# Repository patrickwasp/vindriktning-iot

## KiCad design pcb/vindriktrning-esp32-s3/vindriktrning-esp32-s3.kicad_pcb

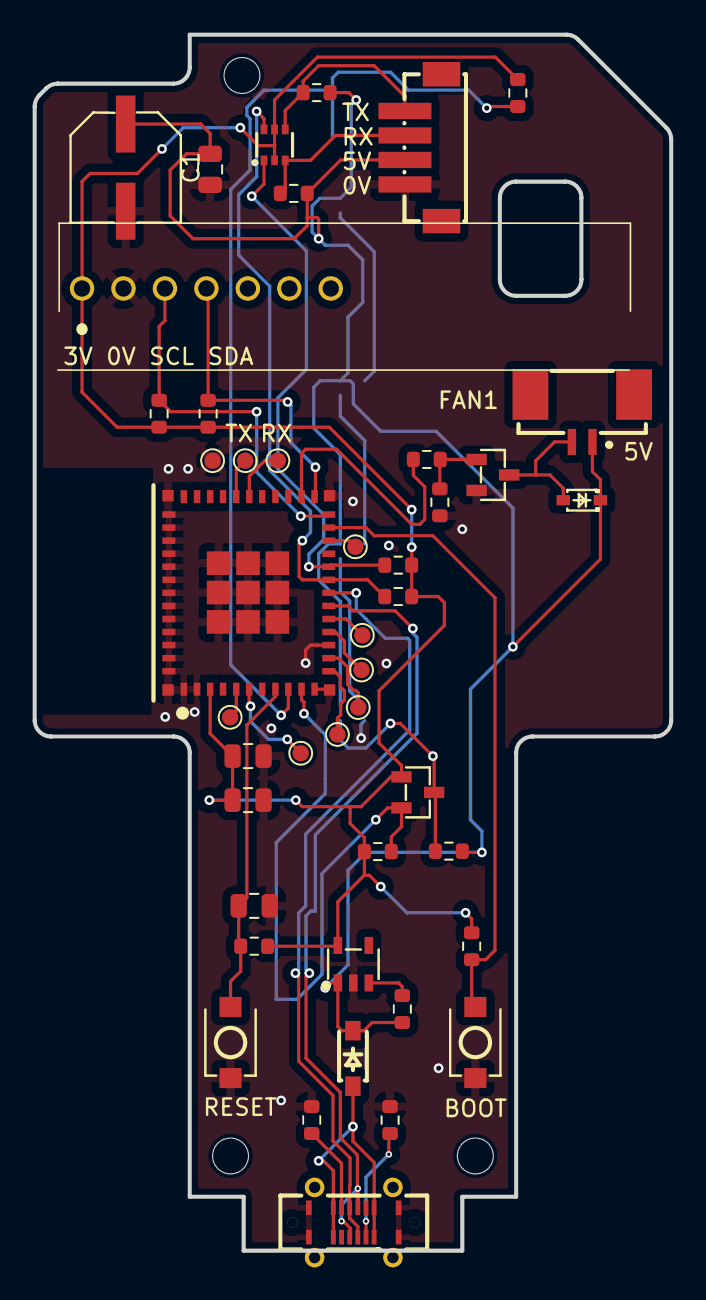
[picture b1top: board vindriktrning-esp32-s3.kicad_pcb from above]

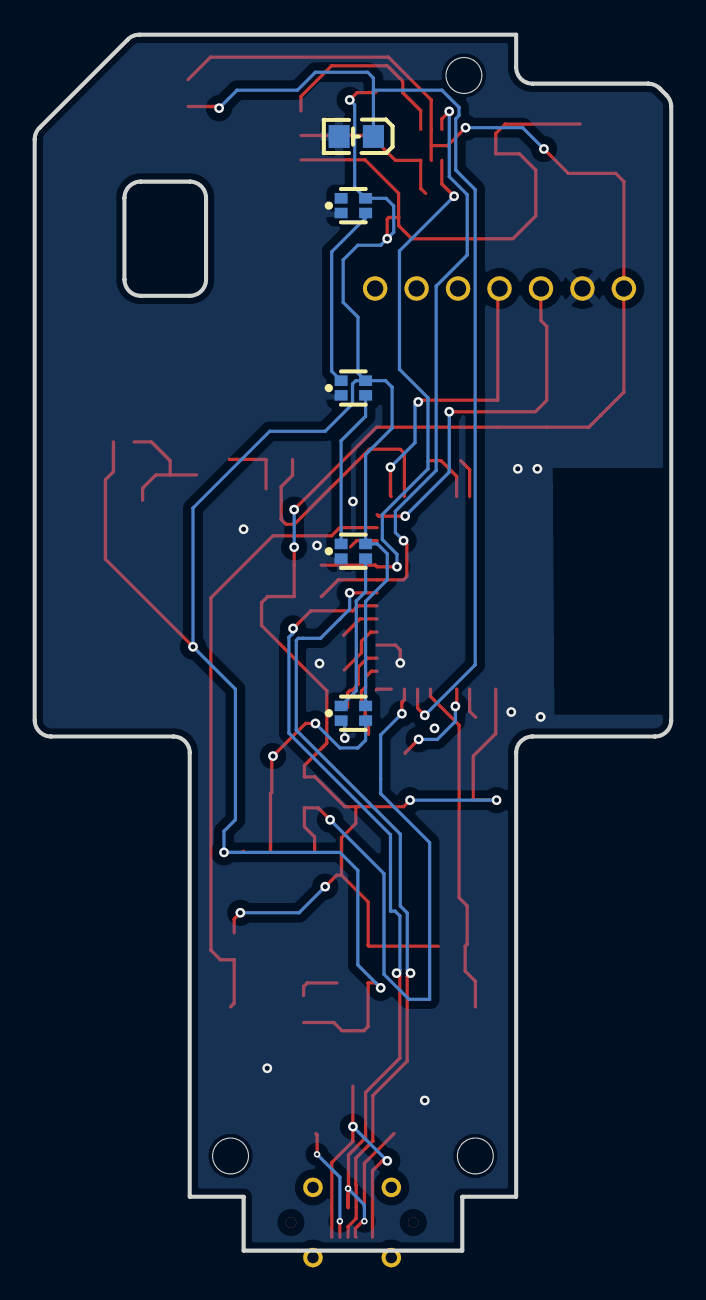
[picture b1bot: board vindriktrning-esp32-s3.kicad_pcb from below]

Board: 4 copper layers, 39.0 x 74.5 mm, 52 parts (5 on the bottom side), 35 nets.

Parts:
C1: 470uF; CAP-SMD_BD6.3-L6.6-W6.6-FD
C2, C3: 10uF; C_0805_2012Metric
C4: 10nF; C_0805_2012Metric
C5: 1uF; C_0805_2012Metric
FAN1: 1.25-2P; CONN-SMD_1.25-2P
H1, H2, H3: MountingHole; MountingHole_2.2mm_M2
IC1: SCD30
J1: P2.5; CONN-SMD_ZH1.5-4AB
J2, J3, J4, J5, J6, J7, J8, J9, J10, J11: Conn_01x01_Pin; TestPoint_Pad_D1.0mm
LED1: D10; LED-SMD_4P-L1.6-W1.5_XL-1615RGBC-WS2812B
LED2: D11; LED-SMD_4P-L1.6-W1.5_XL-1615RGBC-WS2812B
LED3: D12; LED-SMD_4P-L1.6-W1.5_XL-1615RGBC-WS2812B
LED4: D13; LED-SMD_4P-L1.6-W1.5_XL-1615RGBC-WS2812B
Q1: AO3400A_C347475; SOT-23-3_L2.9-W1.3-P1.90-LS2.4-BR
Q2: BSD840NH6327XTSA1; SC-70-6_L2.2-W1.3-P0.65-LS2.1-BR
Q3: BSS138; SOT-23-3_L2.9-W1.3-P1.90-LS2.4-BR
R1, R5, R11, R12, R13: 5.1k; R_0603_1608Metric
R2, R7, R8, R9, R10, R14: 10k; R_0603_1608Metric
R3, R4, R6, R16: 100k; R_0603_1608Metric
R15: 1k; R_0603_1608Metric
SW1: RESET Swtich; SW-SMD_L3.9-W3.0-P4.45
SW2: BOOT Switch; SW-SMD_L3.9-W3.0-P4.45
U1: SMD0805-20; OPTO-SMD_SMD0805-20
U2: D1; SOD-123_L2.7-W1.6-LS3.7-RD-1
U3: 1N5819; SOD-323_L1.7-W1.3-LS2.6-RD-1
U4: RT9080-33GJ5; TSOT-23-5_L2.9-W1.6-P0.95-LS2.8-BL
U6: ESP32-C6-MINI-1-N4; WIFIM-SMD_61P-L16.6-W13.2-P0.80-ESP32-C6-MINI-1-N4
USB1: GT-USB-7055BB; USB-C-TH_GT-USB-7055BB

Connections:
5VIN: U2.2 (A), USB1.A4 (VBUS), USB1.A9 (VBUS), USB1.B4 (VBUS), USB1.B9 (VBUS)
+3V3: C3.1, C4.1, IC1.1 (VDD), Q2.2 (G1), Q2.5 (G2), Q3.1 (G), R2.1, R7.1, R10.1, R11.1, R12.2, R13.2, R14.1, R16.1, U4.5 (VOUT), U6.3 (3V3)
+5V: C1.1, C2.1, FAN1.1, J1.3, LED1.2 (VDD), LED2.2 (VDD), LED3.2 (VDD), LED4.2 (VDD), R6.1, R8.2, R9.2, R15.1, U2.1 (K), U3.1 (C), U4.1 (VIN)
BOOT: R16.2, SW2.2, U6.23 (IO9)
CC1: R1.1, USB1.A5 (CC1)
CC2: R5.1, USB1.B5 (CC2)
D+: U6.18 (IO13), USB1.A6 (D+), USB1.B6 (D+)
D-: U6.17 (IO12), USB1.A7 (D-), USB1.B7 (D-)
FAN: R3.1, U6.26 (IO20)
GND: C1.2, C2.2, C3.2, C4.2, C5.2, IC1.2 (GND), J1.4, J4.1, LED1.3 (GND), LED2.3 (GND), LED3.3 (GND), LED4.3 (GND), Q1.2 (S), R1.2, R4.2, R5.2, SW1.1, SW2.1, U1.1 (E), U4.2 (GND), U6.1 (GND), U6.2 (GND), U6.11 (GND), U6.14 (GND), U6.36 (GND), U6.37 (GND), U6.38 (GND), U6.39 (GND), U6.40 (GND), U6.41 (GND), U6.42 (GND), U6.43 (GND), U6.44 (GND), U6.45 (GND), U6.46 (GND), U6.47 (GND), U6.48 (GND), U6.49 (GND), U6.50 (GND), U6.51 (GND), U6.52 (GND), U6.53 (GND), USB1.A1 (GND), USB1.A12 (GND), USB1.B1 (GND), USB1.B12 (GND)
IO0: J7.1, U6.12 (IO0)
IO1: J8.1, U6.13 (IO1)
IO2: J5.1, U6.5 (IO2)
IO3: J6.1, U6.6 (IO3)
IO6: J9.1, U6.15 (IO6)
IO7: J10.1, U6.16 (IO7)
IO8: J11.1, U6.22 (IO8)
LED_DATA: Q3.2 (S), R14.2, U6.10 (IO5)
LIGHT: R2.2, U1.2 (C), U6.9 (IO4)
unnamed: LED1.4 (DI), Q3.3 (D), R15.2
unnamed: LED1.1 (DO), LED2.4 (DI)
unnamed: LED2.1 (DO), LED3.4 (DI)
unnamed: LED3.1 (DO), LED4.4 (DI)
unnamed: FAN1.2, Q1.3 (D), U3.2 (A)
unnamed: Q1.1 (G), R3.2, R4.1
unnamed: R6.2, U4.3 (EN)
P2.5_RX: J1.2, Q2.3 (D2), R8.1
P2.5_TX: J1.1, Q2.4 (S2), R9.1
RESET: C5.1, R11.2, SW1.2, U6.8 (EN)
RX2: Q2.6 (D1), R10.2, U6.19 (IO14)
RXD0: J3.1, U6.30 (RXD0)
SCL: IC1.3 (TX/_SCL), R12.1, U6.24 (IO18)
SDA: IC1.4 (RX/_SDA), R13.1, U6.25 (IO19)
TX2: Q2.1 (S1), R7.2, U6.20 (IO15)
TXD0: J2.1, U6.31 (TXD0)
